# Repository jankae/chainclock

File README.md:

# chainclock

The chainclock is a very inaccurate clock which displays the time by means of rotating a chain.

The chain-loop consists of 120 links, with a number attached to every 10th link. Since the driving gear has ten teeth, this results in one rotation per hour. After some failed experiments with attaching the gear to the hour hand of a normal clock (it was either too loud, too weak or both), I opted for a 28BYJ-48 stepper motor.

This also called for a microcontroller (ATtiny2313) with the simpliest of programs. To save energy, the motor doesn't continually move. Instead it is only activated whenever a minute has passed. The microcontroller performs a few steps, checks the voltage and goes back to sleep.

The clock is powered by a 3,7V Lipo battery and stops completely if the battery runs low (there is no further indicator, the clock simply stops until the battery is replaced).

## Construction
The central part is the stepper motor (28BYJ-48). Some additional aluminium, a ball bearing to lighten the load on the motor (should be fine even without it) and a teardrop wooden enclosure completes the clock.

## Compiling & Flashing
1. See PCB-files for the pinout of the ISP connector. 
2. Adjust the makefile to your programmer
3. Setting fuses:

  ```
  cd software
  make fuses
  ```
4. Flash the program:

  ```
  make flash
  ```
  ## Operation
  Attach the chain and sit back ;)

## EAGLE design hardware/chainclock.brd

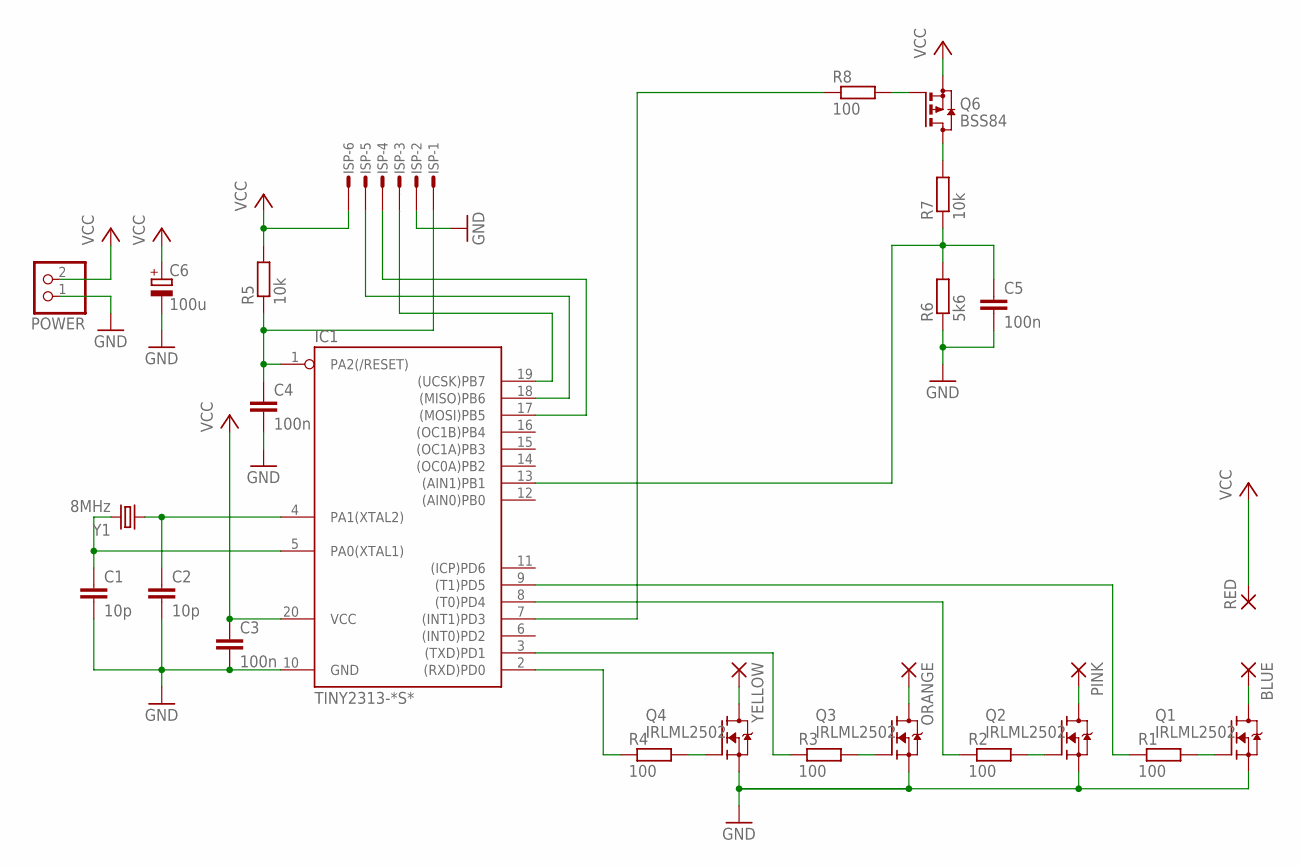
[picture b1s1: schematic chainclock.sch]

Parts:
BLUE: SMD2; SMD1,27-2,54
C1, C2: 10p; C0603
C3, C4, C5: 100n; C0603
C6: 100u; E2,5-6
IC1: TINY2313-*S*; SO20L$
ISP: MICROMATCH-6SMF; MMT-F-SMD-6
ORANGE: SMD2; SMD1,27-2,54
PINK: SMD2; SMD1,27-2,54
POWER: PINHD-1X2/90; 1X02/90
Q1, Q2, Q3, Q4: IRLML2502; SOT23-3
Q6: BSS84; SOT23
R1, R2, R3, R4, R8: 100; R0603
R5, R7: 10k; R0603
R6: 5k6; R0603
RED: SMD2; SMD1,27-2,54
Y1: 8MHz; HC49UP
YELLOW: SMD2; SMD1,27-2,54

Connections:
GND: C1.2, C2.2, C3.2, C4.2, C5.2, C6.-, IC1.10 (GND), ISP.2, POWER.1, Q1.2 (S), Q2.2 (S), Q3.2 (S), Q4.2 (S), R6.1
unnamed: Q3.1 (G), R3.2
unnamed: Q4.1 (G), R4.2
unnamed: Q2.1 (G), R2.2
unnamed: Q1.1 (G), R1.2
unnamed: C4.1, IC1.1 (PA2(/RESET)), ISP.1, R5.1
unnamed: Q4.3 (D), YELLOW.1
unnamed: ORANGE.1, Q3.3 (D)
unnamed: PINK.1, Q2.3 (D)
unnamed: BLUE.1, Q1.3 (D)
unnamed: C2.1, IC1.4 (PA1(XTAL2)), Y1.1
unnamed: C1.1, IC1.5 (PA0(XTAL1)), Y1.2
unnamed: IC1.19 ((UCSK)PB7), ISP.3
unnamed: C5.1, IC1.13 ((AIN1)PB1), R6.2, R7.1
unnamed: IC1.9 ((T1)PD5), R1.1
unnamed: IC1.8 ((T0)PD4), R2.1
unnamed: IC1.2 ((RXD)PD0), R4.1
unnamed: Q6.3 (D), R7.2
unnamed: Q6.1 (G), R8.2
unnamed: IC1.7 ((INT1)PD3), R8.1
unnamed: IC1.3 ((TXD)PD1), R3.1
unnamed: IC1.17 ((MOSI)PB5), ISP.4
unnamed: IC1.18 ((MISO)PB6), ISP.5
VCC: C3.1, C6.+, IC1.20 (VCC), ISP.6, POWER.2, Q6.2 (S), R5.2, RED.1

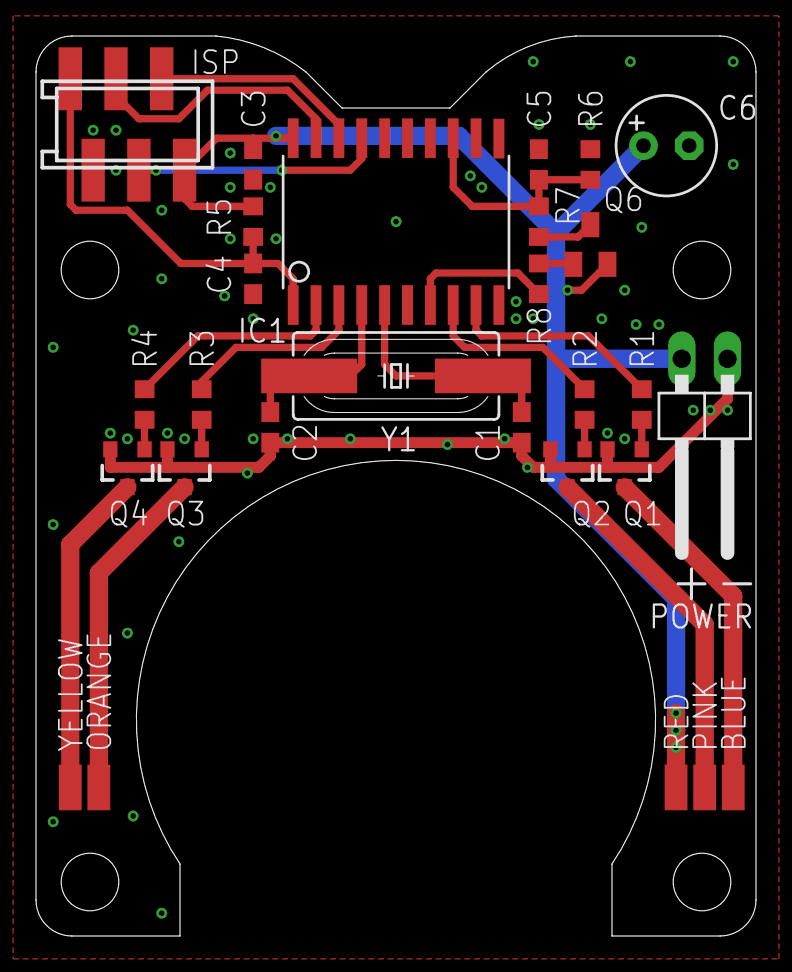
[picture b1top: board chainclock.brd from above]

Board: 2 copper layers, 40.0 x 50.0 mm, 28 parts (0 on the bottom side), 24 nets.

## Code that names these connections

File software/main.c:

#include <avr/io.h>
#include <avr/interrupt.h>
#include <avr/sleep.h>
#include <util/delay.h>

#define BLUE_HIGH()		(PORTD |= (1<<PD5))
#define BLUE_LOW()		(PORTD &= ~(1<<PD5))

#define PINK_HIGH()		(PORTD |= (1<<PD4))
#define PINK_LOW()		(PORTD &= ~(1<<PD4))

#define ORANGE_HIGH()		(PORTD |= (1<<PD1))
#define ORANGE_LOW()		(PORTD &= ~(1<<PD1))

#define YELLOW_HIGH()		(PORTD |= (1<<PD0))
#define YELLOW_LOW()		(PORTD &= ~(1<<PD0))

/* counter for the motor steps */
/* 1019/15 steps per minute needed */
/* needed rotations*15 -> 1019 of this per minute */
uint16_t neededRotations15;

uint8_t minuteParts;
uint8_t minuteFlag;

uint8_t stepCnt = 0;

uint8_t batteryLow = 0;

void waitms(uint16_t ms) {
	for (; ms > 0; ms--)
		_delay_ms(1);
}

void stopMotor(void) {
	ORANGE_LOW();
	YELLOW_LOW();
	PINK_LOW();
	BLUE_LOW();
}

void moveStep(void) {
	stepCnt += 1;
	if (stepCnt >= 8)
		stepCnt = 0;
	switch (stepCnt) {
	case 0:
		ORANGE_HIGH();
		YELLOW_LOW();
		PINK_LOW();
		BLUE_LOW();
		break;
	case 1:
		ORANGE_HIGH();
		YELLOW_HIGH();
		PINK_LOW();
		BLUE_LOW();
		break;
	case 2:
		ORANGE_LOW();
		YELLOW_HIGH();
		PINK_LOW();
		BLUE_LOW();
		break;
	case 3:
		ORANGE_LOW();
		YELLOW_HIGH();
		PINK_HIGH();
		BLUE_LOW();
		break;
	case 4:
		ORANGE_LOW();
		YELLOW_LOW();
		PINK_HIGH();
		BLUE_LOW();
		break;
	case 5:
		ORANGE_LOW();
		YELLOW_LOW();
		PINK_HIGH();
		BLUE_HIGH();
		break;
	case 6:
		ORANGE_LOW();
		YELLOW_LOW();
		PINK_LOW();
		BLUE_HIGH();
		break;
	case 7:
		ORANGE_HIGH();
		YELLOW_LOW();
		PINK_LOW();
		BLUE_HIGH();
		break;
	}
}

void moveOneMinute(void) {
	neededRotations15 += 1019;
	minuteParts = 0;
	minuteFlag = 0;
	uint8_t additionalRotations = neededRotations15 / 15;
	neededRotations15 -= additionalRotations * 15;
	/* enable analog comparator for detecting low battery */
	ACSR &= ~(1 << ACD);
	/* select bandgap reference */
	ACSR |= (1 << ACBG);
	/* enable voltage divider */
	PORTD &= ~(1 << PD3);
	while (additionalRotations > 0) {
		moveStep();
		waitms(3);
		additionalRotations--;
	}
	if (ACSR & (1 << ACO)) {
		/* bandgap (1.1V) is higher than battery voltage after voltage divider */
		/* -> battery low */
		batteryLow = 1;
	}
	stopMotor();
	/* disable ADC and voltage divider */
	PORTD |= (1 << PD3);
	ACSR |= (1 << ACD);
	ACSR &= ~(1 << ACBG);
}

int main(void) {
	neededRotations15 = 0;
	/* disable analog comparator to save energy */
	ACSR |= (1 << ACD);
	/* Set motor pins at output */
	DDRD |= 0b00110011;
	/* Set voltage divider enable pin as output */	
	DDRD |= 0b00001000;
	/* enable all pullups on unused pins */
	PORTD = 0b11000100;
	PORTB = 0b11111101;
	/* disable voltage divider */
	PORTD |= (1 << PD3);
	/* disable digital input buffer on PB1 (AIN1) */
	DIDR |= (1 << AIN1D);
	/* configure timer 1 to use as wake-up call each minute */
	/* prescaler = 64, CTC mode */
	OCR1A = 62499; /* -> 15 compare matches per minute */
	TCCR1B |= (1 << CS11) | (1 << CS10) | (1 << WGM12);
	TIMSK |= (1 << OCIE1A);
	/* configure sleep mode */
	set_sleep_mode(SLEEP_MODE_IDLE);
	sei();
	while (1) {
		sleep_mode()
		;
		if (minuteFlag)
			moveOneMinute();
		if (batteryLow) {
			/* battery voltage is too low */
			/* -> disable all periphery and enter deep sleep mode */
			stopMotor();
			TCCR1B = 0;
			cli();
			set_sleep_mode(SLEEP_MODE_PWR_DOWN);
			sleep_mode()
			;
			/* should never reach this point */
			for (;;)
				;
		}
	}
}
ISR(TIMER1_COMPA_vect) {
	minuteParts++;
	if (minuteParts >= 15) {
		minuteFlag = 1;
		minuteParts -= 15;
	}
}

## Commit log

2017-03-24 Makefile + gitignore extended
2017-03-24 Pins adapted to new layout
2017-03-24 voltage divider resistor values fixed
2017-03-24 Gimp exclusion + images
2017-04-17 Gerber files
2017-04-17 Motor delay reduced
2017-04-17 additional images
2017-07-22 Motor step time increased
2019-07-10 gitignore update

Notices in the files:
parts and their libraries:
xmaker: Licensing: CC v3.0 Attribution-Share Alike
http://creativecommons.org/licenses/by-sa/3.0
